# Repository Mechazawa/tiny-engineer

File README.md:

# Tiny Engineer

> Give your AI coding agent a body.

**[Watch the demo](https://youtu.be/RX_QRxdXMjg)** · [Build your own](#build-your-own) · [Community builds](#community-builds) · [How it works](#how-it-works)

A small robot on your desk. It moves, changes its face, and rings a bell as your coding AI agent works.

| Your agent… | The robot… |
| --- | --- |
| Reads files | Looks around |
| Writes code | Types |
| Thinks or waits | Looks up |
| Finishes the task | Rings the bell |

Open source. Print the body, plug the ESP32, servos, OLED, and speaker into the [main control board](docs/hardware/main-control-board.md), flash it, and it joins your Wi-Fi.

**Works with** [Claude Code](docs/integration.md#4-claude-code-dedicated-script) · [Cursor](docs/hooks.md) · [Antigravity](docs/integration.md#3-antigravity-cli-dedicated-script) — or Codex, Windsurf, and any script that can POST ([integration guide](docs/integration.md)).

## Build your own

| | |
| --- | --- |
| **Parts (electronics + 5× SG90 Servos)** | [shopping list](docs/shopping.md): [main control board](docs/hardware/order-main-control-board.md) plus ESP32, servos, OLED, and speaker |
| **Also needed** | 3D printer + filament, or [order prints](docs/3d/order-parts.md); M2 screws; **5 V / ≥2 A** USB supply |
| **Tools** | Plug in the ESP32, servos, OLED, and speaker on the [main control board](docs/hardware/main-control-board.md). Want to add extra modules? [advanced wiring](docs/hardware/wiring.md) |
| **Difficulty** | **Medium** - fair first hardware project for a software engineer, not a one-LED kit. Optional primer: [From Code to Circuits](docs/hardware-for-software-engineers/README.md) |

The default build uses the open-source main control board. Order it from any fab ([how to order](docs/hardware/order-main-control-board.md) · [KiCad](hardware/boards/main-control-board/)). 

If a ~$15–20 assembled board like this would be useful to you, [Vote here 👍 →](https://github.com/jamro/tiny-engineer/discussions/50) → I’m using the interest to decide whether it’s worth developing further.

**Print → Connect → Flash → Assemble** - step-by-step: **[Getting started](docs/getting-started.md)**.

## Community builds

Finished builds, mods, and desk setups live in **[Show and tell](https://github.com/jamro/tiny-engineer/discussions/categories/show-and-tell)** on GitHub Discussions - browse what others made and post photos of yours.

**Built one? [Share in Show and tell →](https://github.com/jamro/tiny-engineer/discussions/categories/show-and-tell)**

## Roadmap

What we are building toward:

- **More agent integrations** - one-command hooks for more IDEs and CLIs
- **Simplified build process** - easier assembly and setup for quicker builds
- **New characters / bodies** - alternate shells and mods
- **Multi-agent desk** - more than one tiny teammate

**[Star Tiny Engineer](https://github.com/jamro/tiny-engineer)** to follow the build.

## How it works

Your agent (or a hook script) sends poses over HTTP. The **ESP32-C3** is a small Wi-Fi computer on the robot — one chip that runs the program, joins your network, hosts REST API, and drives the servos, the face, and the speaker.

**Clients**

- **Cursor** - hooks → `tiny-engineer-cursor` → Wi-Fi
- **Antigravity** - lifecycle hooks → `tiny-engineer-antigravity` → Wi-Fi
- **Claude Code** - project hooks → `tiny-engineer-claude-code` → Wi-Fi
- **Bring your own** - any tool that can `POST` to `/anim`

Details: [Integrations](docs/integration.md) · [HTTP API](docs/api.md) · [Cursor hooks](docs/hooks.md)

## Documentation

| You want to… | Start here |
| --- | --- |
| Build the robot | [Getting started](docs/getting-started.md) |
| Buy parts | [Shopping list](docs/shopping.md) |
| Flash the board | **[Web flash](https://jamro.github.io/tiny-engineer/flash/)** · [Flash](docs/flash.md) |
| Assemble the prints | [Assembly](docs/3d/assembly.md) |
| Print the parts | [3D models](3d_models/README.md) |
| Hook up an agent | [Integrations](docs/integration.md) |
| Call the HTTP API | [API](docs/api.md) |
| Anything else | [Docs index](docs/README.md) |

Print it, connect it, change the CAD, or hook up another agent. Issues and PRs welcome - especially new integrations. [CONTRIBUTING.md](CONTRIBUTING.md) · [SECURITY.md](SECURITY.md) · [CODE_OF_CONDUCT.md](CODE_OF_CONDUCT.md)

## License

- **Software** (firmware, integrations, scripts, documentation) — [MIT](LICENSE)
- **Hardware designs** (CAD source and printables in [`3d_models/`](3d_models/) and under [`mods/*/3d_models/`](mods/); KiCad PCBs in [`hardware/`](hardware/)) — [CERN-OHL-S-2.0](3d_models/LICENSE)

See [LICENSING.md](LICENSING.md) for scope and effective date. The **Tiny Engineer** name and logo are not licensed - see [TRADEMARK.md](TRADEMARK.md).

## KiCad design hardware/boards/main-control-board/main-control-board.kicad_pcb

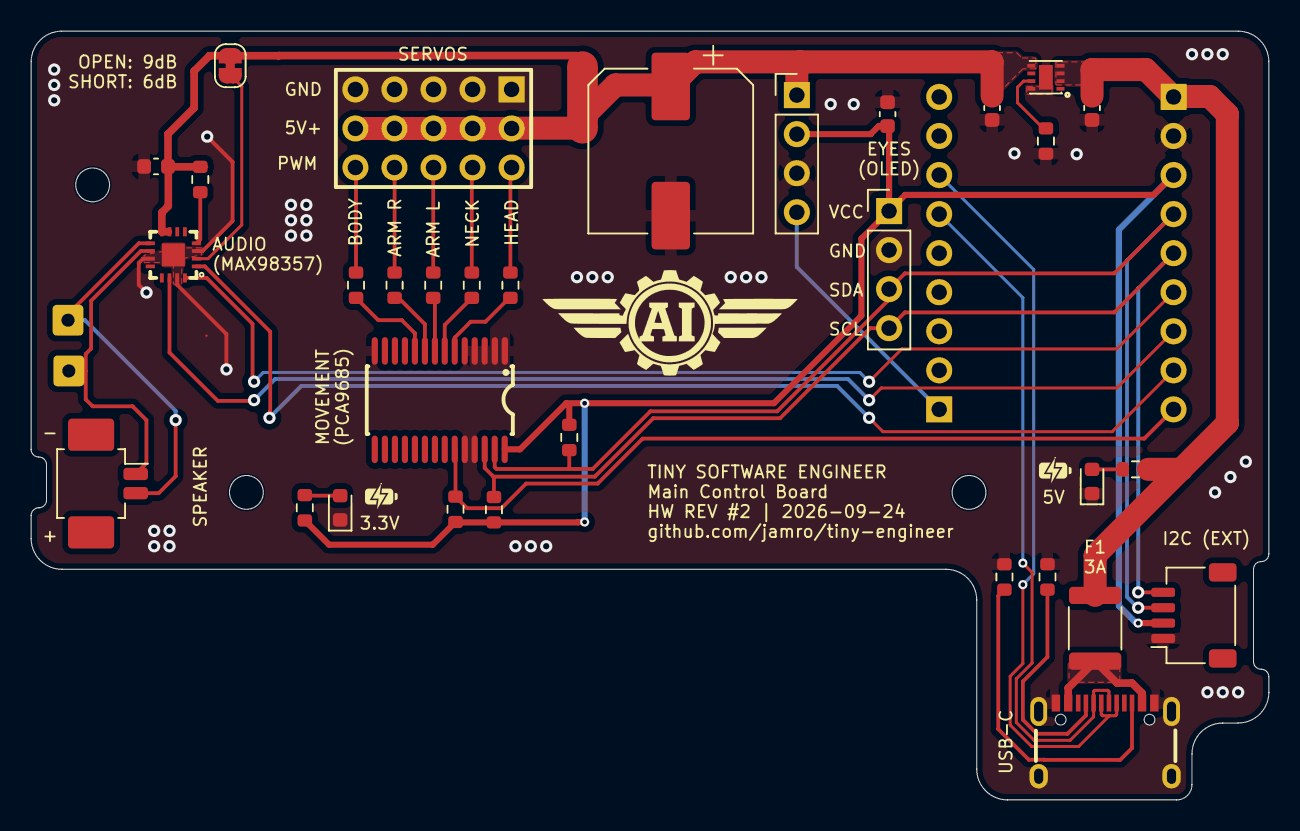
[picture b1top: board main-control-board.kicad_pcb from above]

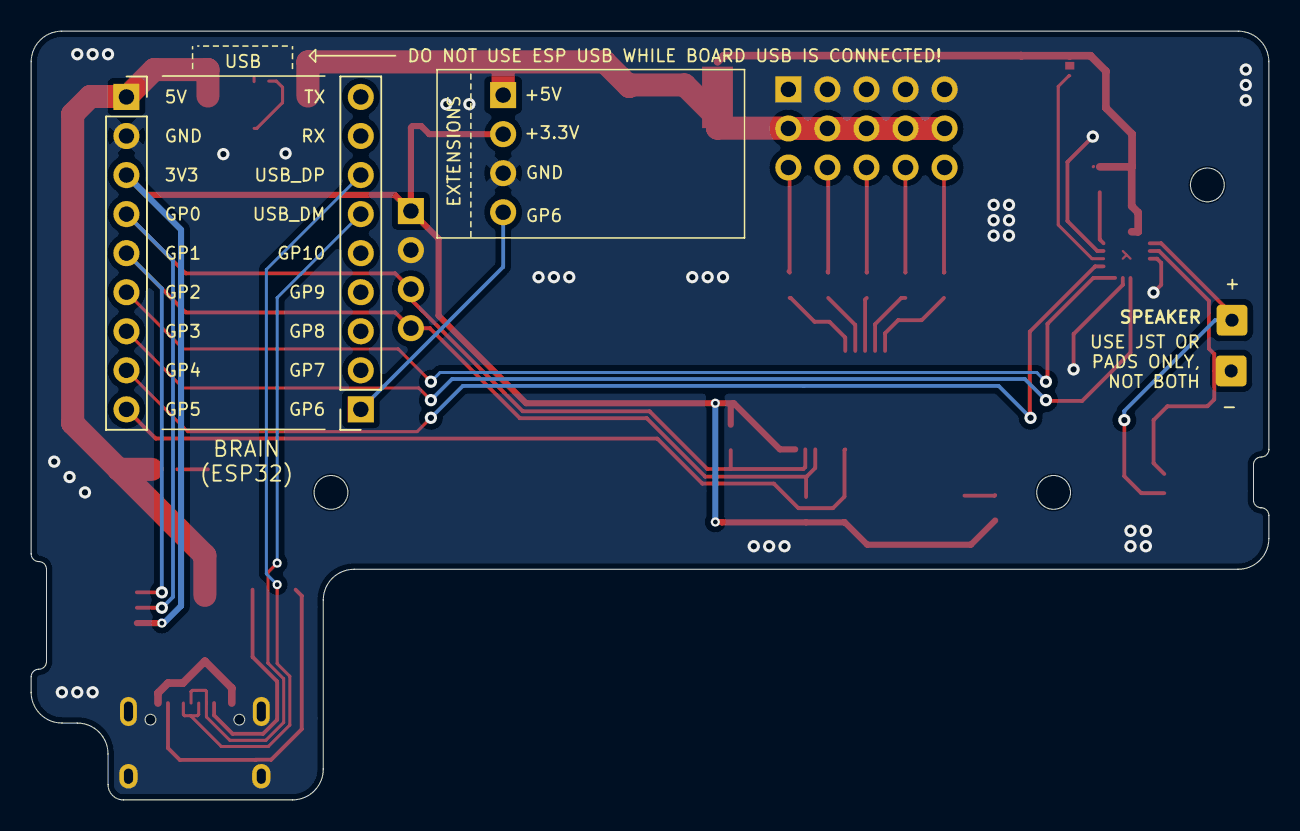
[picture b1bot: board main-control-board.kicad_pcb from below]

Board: 2 copper layers, 80.5 x 50.0 mm, 40 parts (2 on the bottom side), 34 nets.

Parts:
C1, C3, C4, C5: 100nF; C_0603_1608Metric
C2: 1000uF; CP_Elec_10x10.5
D1, D2: LED; LED_0603_1608Metric
F1: 3A PPTC; Fuse_1812_4532Metric
H1, H2, H3: MountingHole; MountingHole_2.2mm_M2
J1: Conn_01x02_Pin_Speaker; Molex_PicoBlade_53261-0271_1x02-1MP_P1.25mm_Horizontal
J2: Conn_OLED; PinHeader_1x04_P2.54mm_Vertical
J3: Conn_extension; JST_SH_SM04B-SRSS-TB_1x04-1MP_P1.00mm_Horizontal
J4: Conn_extension_2; PinHeader_1x04_P2.54mm_Vertical
J7, J8: Conn_ESP32; PinSocket_1x09_P2.54mm_Vertical
JP1: SolderJumper_gain_6dB_limit; SolderJumper-2_P1.3mm_Bridged_RoundedPad1.0x1.5mm
NT1: NetTie_2; NetTie-2_SMD_Pad2.0mm
R1, R2: 5.1k; R_0603_1608Metric
R3: 10k; R_0603_1608Metric
R4, R5: 4.7k; R_0603_1608Metric
R6, R7, R8, R9, R10: 220; R_0603_1608Metric
R11: 2.2k; R_0603_1608Metric
R12: 1M; R_0603_1608Metric
R13, R14: 1k; R_0603_1608Metric
TP1, TP2: TestPoint; SolderWire-0.25sqmm_1x01_D0.65mm_OD2mm
U1: PCA9685PW,118; TSSOP-28_L9.7-W4.4-P0.65-LS6.4-TL
U2: HX PZ2.54-3X5P ZZ; HDR-TH_15P-P2.54-V-M-R3-C5-S7.5
U3: MAX98357AETE+T; TQFN-16_L3.0-W3.0-P0.50-BL-EP1.5
U4: TPS259571DSGR; WSON-8_L2.0-W2.0-P0.50-TL-EP
USB1: TYPE-C 16PIN 2MD; USB-C-SMD_TYPE-C-16PIN-2MD-073

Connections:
+3.3V: C1.2, J2.1, J3.2, J4.2, J7.3, R3.1, R4.1, R5.1, R13.1, U1.28 (VDD)
+5V: C4.2, F1.1, J7.1, R11.1, U4.2 (EN/UVLO), U4.3 (IN), U4.4 (IN)
/Audio/AUDIO_5V: C3.2, JP1.1 (A), NT1.2, R12.1, U3.7 (VDD), U3.8 (VDD)
/ESP32/GP5: J7.9, R3.2, U1.23 (~OE)
/ESP32/GP6: J4.4, J8.1
/I2C_SCL: J2.4, J3.4, J7.5, R4.2, U1.26 (SCL)
/I2C_SDA: J2.3, J3.3, J7.4, R5.2, U1.27 (SDA)
/I2S_BCLK: J7.6, U3.16 (BCLK)
/I2S_DIN: J7.8, U3.1 (DIN)
/I2S_LRC: J7.7, U3.14 (LRCLK)
/PCA/SERVO_5V: C2.1, C5.2, J4.1, NT1.1, U2.2, U2.5, U2.8, U2.11, U2.14, U4.5 (OUT)
/USB/USB_VBUS: F1.2, USB1.A4B9 (VBUS), USB1.B4A9 (VBUS)
/USB_D+: J8.7, USB1.A6 (Dp1), USB1.B6 (Dp2)
/USB_D-: J8.6, USB1.A7 (Dn1), USB1.B7 (Dn2)
GND: C1.1, C2.2, C3.1, C4.1, C5.1, D1.1 (K), D2.1 (K), J2.2, J3.1, J4.3, J7.2, R1.1, R2.1, R14.2, U1.1 (A0), U1.2 (A1), U1.3 (A2), U1.4 (A3), U1.5 (A4), U1.14 (VSS), U1.24 (A5), U1.25 (EXTCLK), U2.1, U2.4, U2.7, U2.10, U2.13, U3.3 (GND), U3.11 (GND), U3.15 (GND), U3.17 (EP), U4.8 (GND), U4.9 (GND), USB1.13 (EH), USB1.14 (EH), USB1.A1B12 (GND), USB1.B1A12 (GND)
unnamed: D1.2 (A), R11.2
unnamed: D2.2 (A), R13.2
unnamed: J1.1, TP1.1 (1_1), U3.10 (OUTN)
unnamed: J1.2, TP2.1 (1_1), U3.9 (OUTP)
unnamed: JP1.2 (B), U3.2 (GAIN_SLOT)
unnamed: R6.2, U2.3
unnamed: R7.2, U2.6
unnamed: R8.2, U2.9
unnamed: R9.2, U2.12
unnamed: R10.2, U2.15
unnamed: R6.1, U1.6 (LED0)
unnamed: R7.1, U1.7 (LED1)
unnamed: R8.1, U1.8 (LED2)
unnamed: R9.1, U1.9 (LED3)
unnamed: R10.1, U1.10 (LED4)
unnamed: R12.2, U3.4 (~SD_MODE)
unnamed: R14.1, U4.7 (ILM)
unnamed: R1.2, USB1.A5 (CC1)
unnamed: R2.2, USB1.B5 (CC2)

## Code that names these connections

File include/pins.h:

#pragma once

#include <cstdint>

// =====================================================
// PINOUT
// =====================================================

// I2C -> PCA9685 + OLED
constexpr int I2C_SDA = 0;   // GP0
constexpr int I2C_SCL = 1;   // GP1

// I2S -> MAX98357A
constexpr int I2S_BCLK = 2;  // GP2
constexpr int I2S_LRC  = 3;  // GP3
constexpr int I2S_DIN  = 4;  // GP4

// Built-in WS2812 RGB
constexpr int RGB_LED_PIN = 10;

// PCA9685 output enable (active LOW). GP5 → OE pending; schematic/PCB do not implement that net.
constexpr bool PCA9685_OE_WIRED = false;
constexpr int PCA9685_OE_PIN = 5;

// =====================================================
// AUDIO
// =====================================================

// assets/ ships 44100 Hz WAVs; scripts/audio_pack.py halves them while packing LittleFS.
constexpr int SAMPLE_RATE = 22050;

// =====================================================
// PCA9685 / SERVOS
// =====================================================

constexpr uint8_t PCA9685_ADDRESS = 0x40;

constexpr int SERVO_STEP_MS = 10;

// Boot centering / sleep-pose rate (deg/s)
constexpr float SERVO_BOOT_SPEED_DEG_S = 35.0f;

// Servo pulse range
constexpr int SERVO_MIN_US = 800;
constexpr int SERVO_MAX_US = 2200;

// =====================================================
// OLED
// =====================================================

constexpr int OLED_WIDTH  = 128;
constexpr int OLED_HEIGHT = 32;
constexpr uint8_t OLED_ADDRESS = 0x3C;
